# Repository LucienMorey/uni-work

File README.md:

# uni-work

A collation of my software related work and assignments while at University of Technology Sydney.

## Contributors

Some parts of this work were completed in conjunction with my peers.

ur3_cup_ball - Jesse Mcnamara, Nicholas Polivis, George Sheslow

ball_and_beam_control - George Sheslow

mx2_turtle_slam - Jesse Mcnamara, Braeden Knox

jlm - Jesse Mcnamara

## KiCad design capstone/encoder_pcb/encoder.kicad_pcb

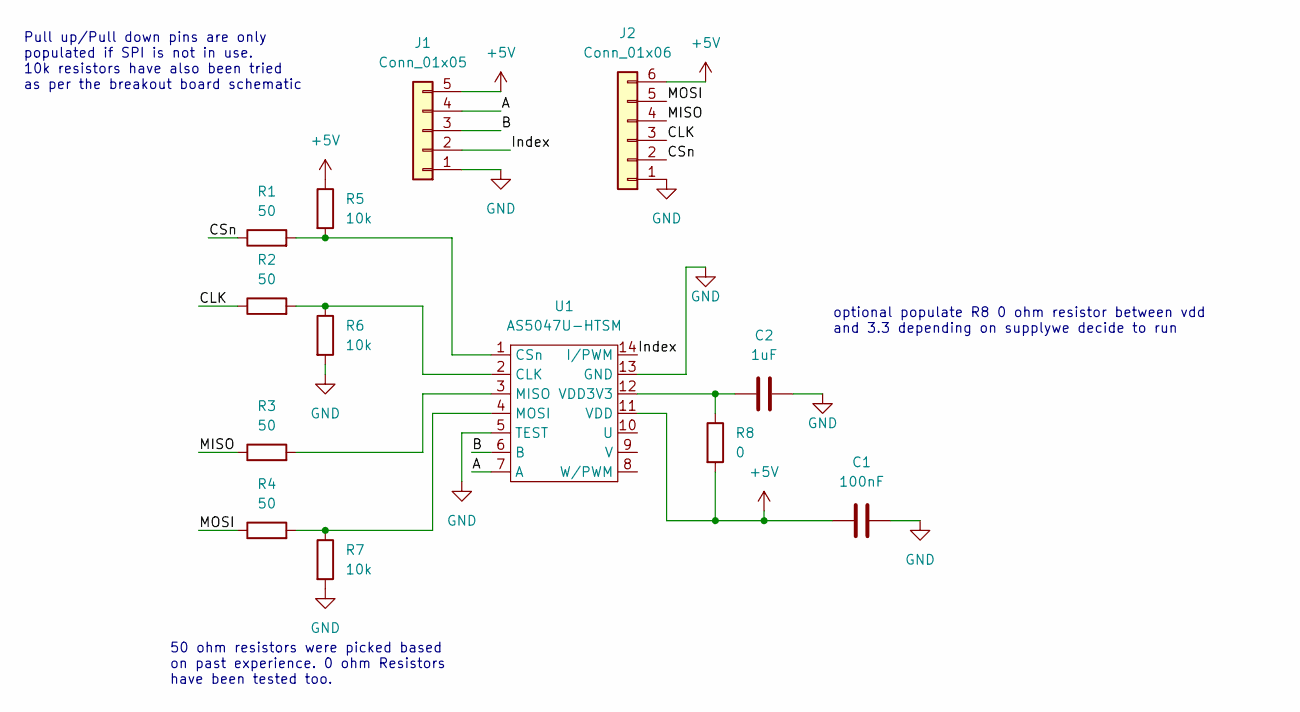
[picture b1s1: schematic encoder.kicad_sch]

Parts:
C1: 100nF; C_0805_2012Metric
C2: 1uF; C_0805_2012Metric
J1: Conn_01x05; j_01x05
J2: Conn_01x06; j_01x06
R1, R2, R3, R4: 50; R_0603_1608Metric
R5, R6, R7: 10k; R_0603_1608Metric
R8: 0; C_0603_1608Metric
U1: AS5047U-HTSM; TSSOP-14_4.4x5mm_P0.65mm

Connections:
+5V: C1.1, J1.5, J2.6, R5.1, R8.2, U1.11 (VDD)
/A: J1.4, U1.7 (A)
/B: J1.3, U1.6 (B)
/CLK: J2.3, R2.1
/CSn: J2.2, R1.1
/Index: J1.2, U1.14 (I/PWM)
/MISO: J2.4, R3.1
/MOSI: J2.5, R4.1
GND: C1.2, C2.2, J1.1, J2.1, R6.2, R7.2, U1.5 (TEST), U1.13 (GND)
unnamed: R1.2, R5.2, U1.1 (CSn)
unnamed: R2.2, R6.1, U1.2 (CLK)
unnamed: R3.2, U1.3 (MISO)
unnamed: R4.2, R7.1, U1.4 (MOSI)
unnamed: C2.1, R8.1, U1.12 (VDD3V3)

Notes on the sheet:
50 ohm resistors were picked based on past experience. 0 ohm Resistors have been tested too.
optional populate R8 0 ohm resistor between vdd and 3.3 depending on supplywe decide to run
Pull up/Pull down pins are only populated if SPI is not in use. 10k resistors have also been tried as per the breakout board schematic

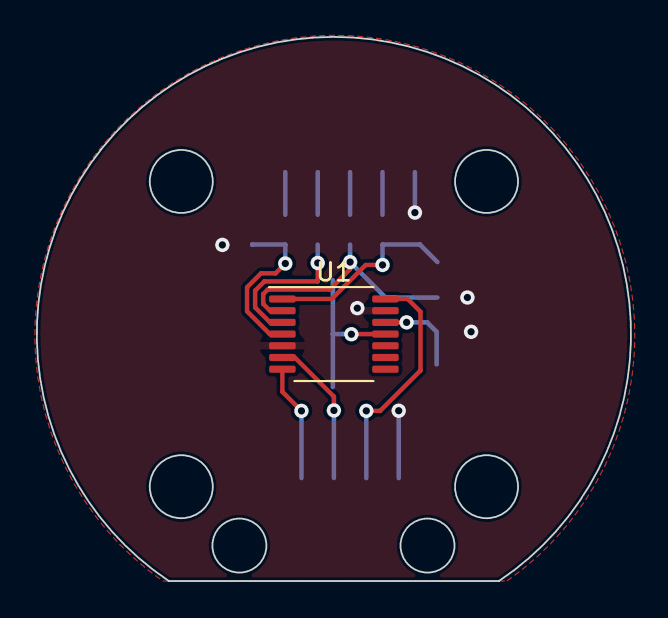
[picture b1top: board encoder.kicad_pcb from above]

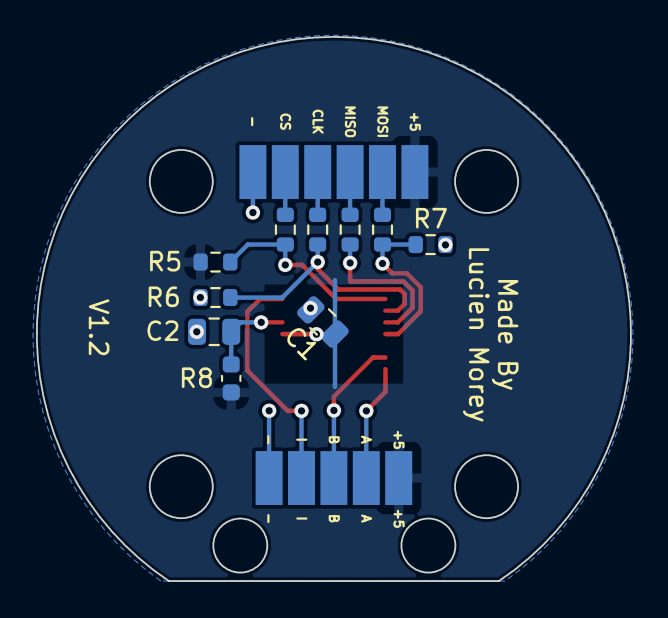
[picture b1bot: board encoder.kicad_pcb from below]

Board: 2 copper layers, 33.0 x 30.2 mm, 13 parts (12 on the bottom side), 14 nets.

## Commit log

2024-09-07 dump of content from my github
2024-09-07 dump copy of coursework from pfms
2026-04-26 dump
